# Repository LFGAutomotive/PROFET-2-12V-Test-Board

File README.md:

# Infineon PROFET +2 12V PMIC Test Board
This is a KiCad project for a pcb to test Infineon PROFET +2 12V PMIC packages. This board uses a Raspberry Pi Pico as the main testing MCU.

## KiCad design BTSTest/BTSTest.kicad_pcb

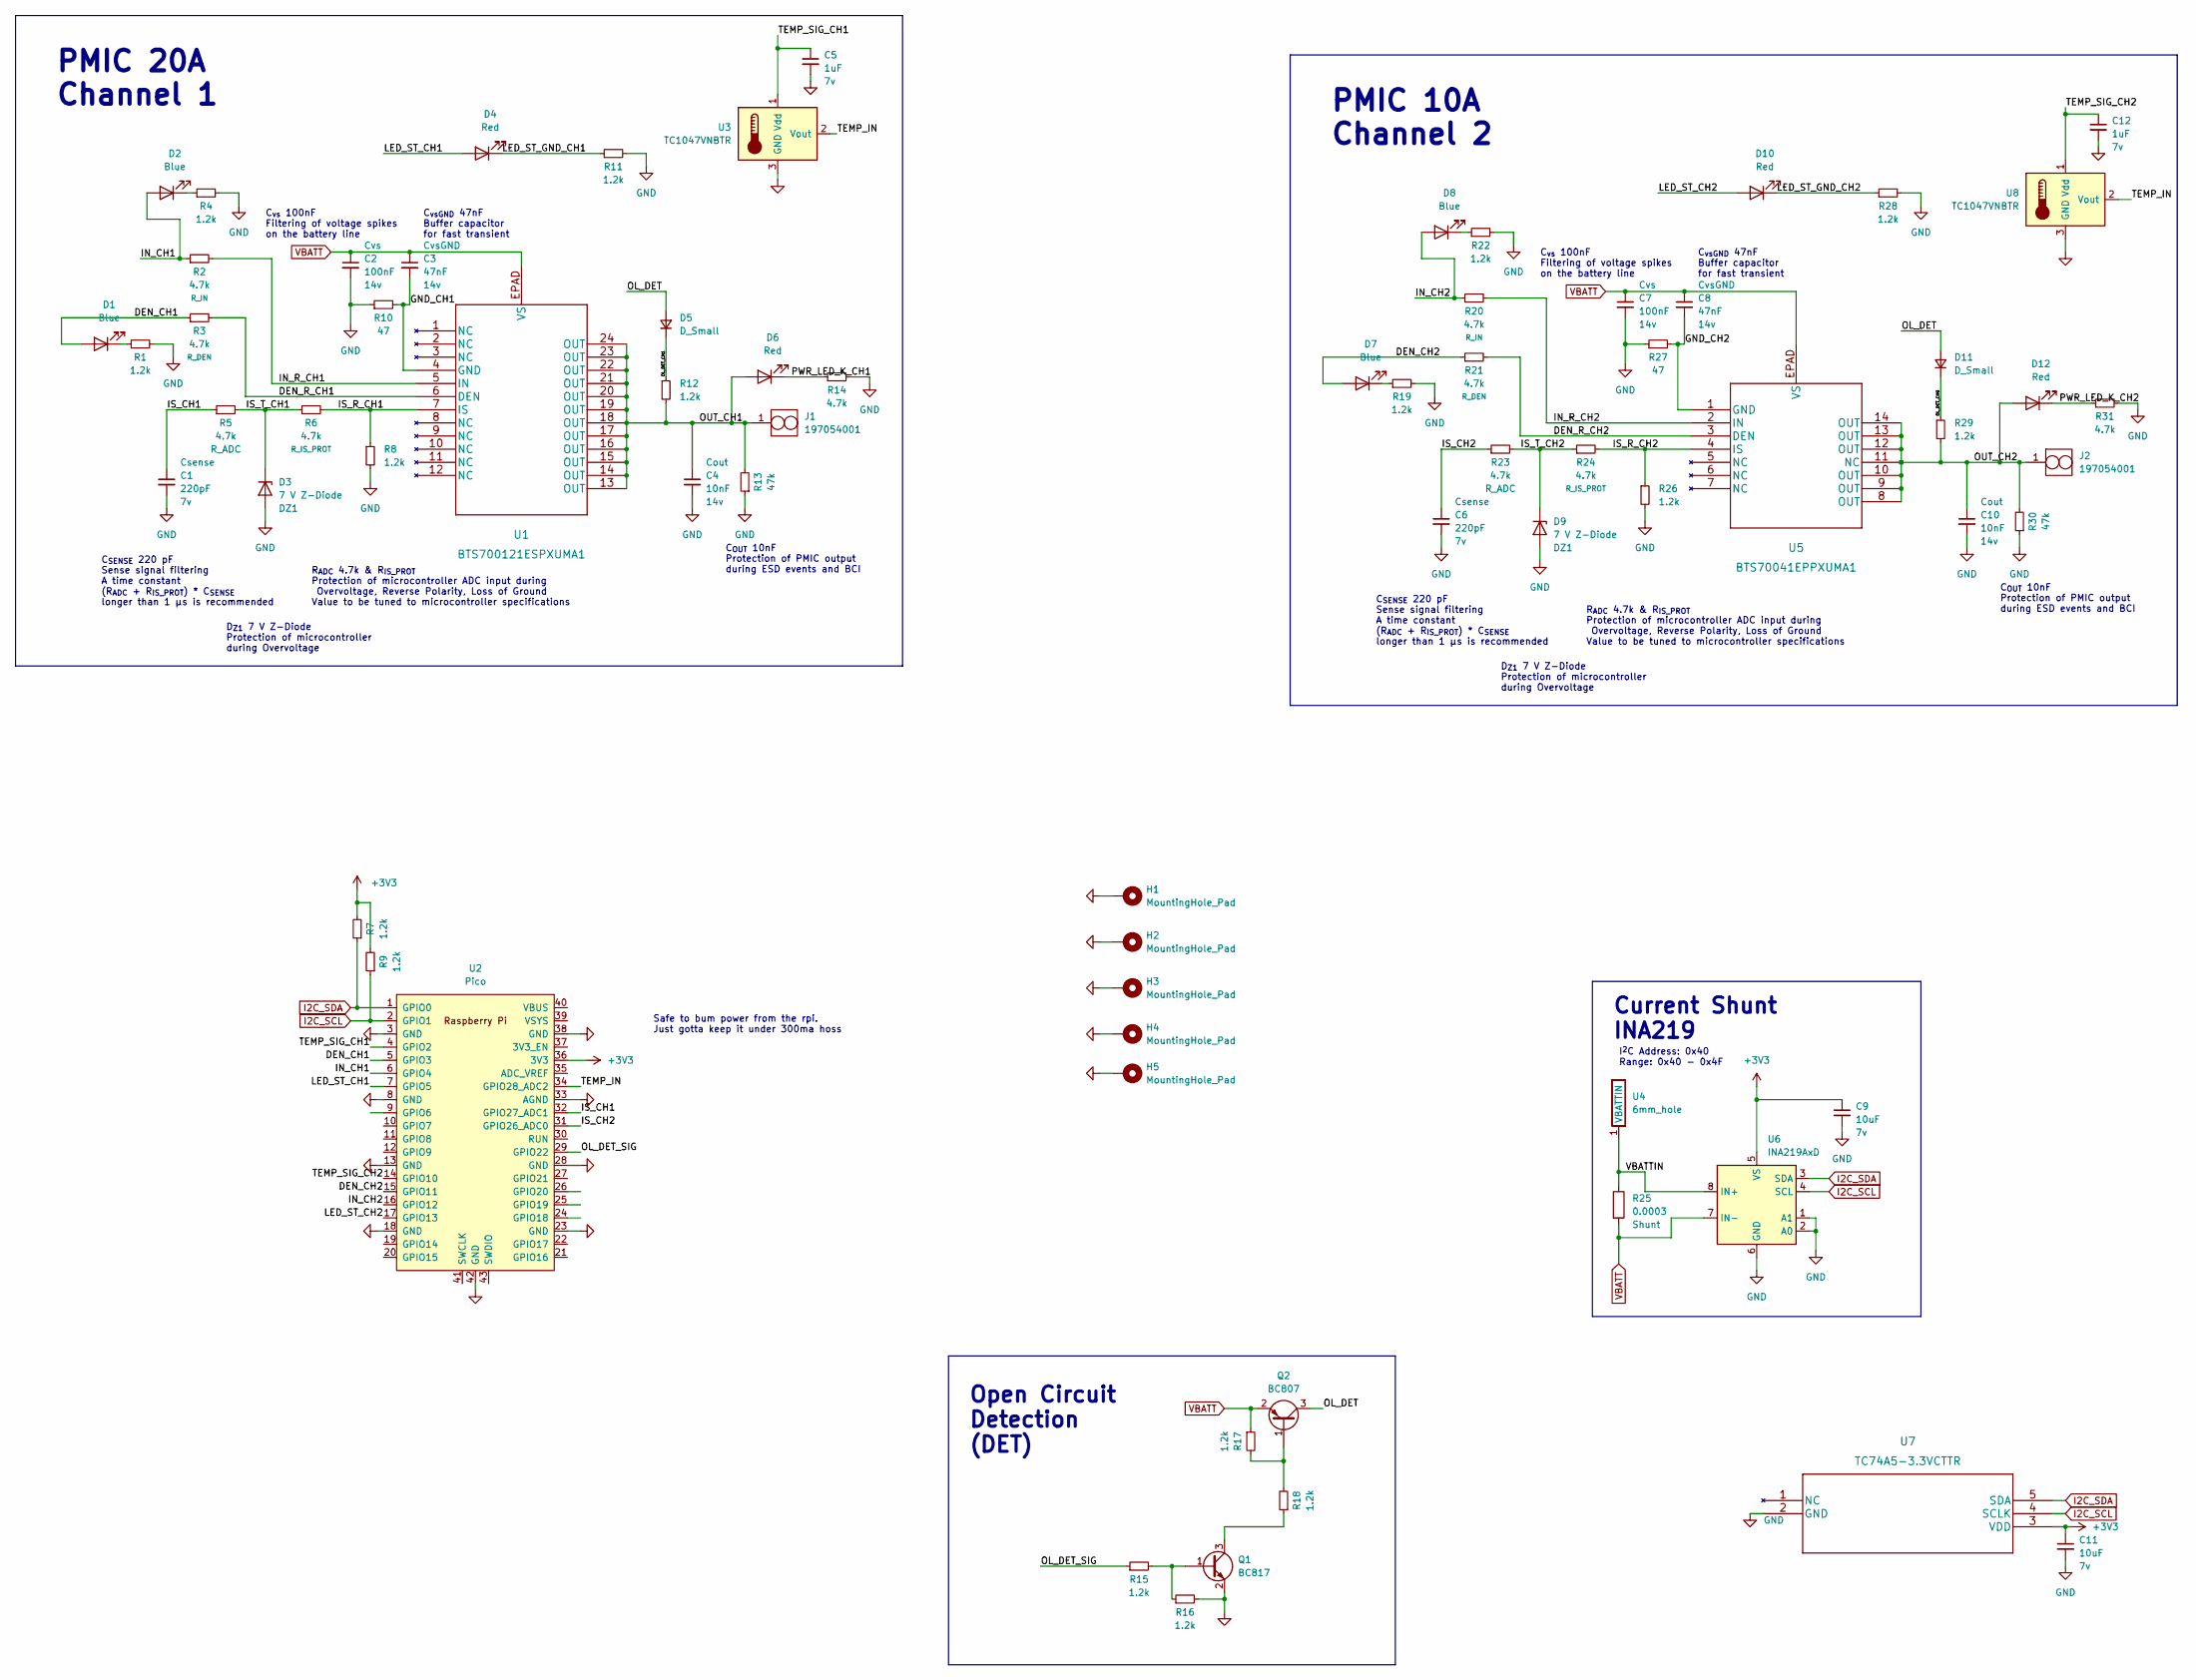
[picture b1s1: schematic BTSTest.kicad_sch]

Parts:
C1, C6: 220pF; C_0603_1608Metric; Voltage 7v
C2, C7: 100nF; C_0603_1608Metric; Voltage 14v
C3, C8: 47nF; C_0603_1608Metric; Voltage 14v
C4, C10: 10nF; C_0603_1608Metric; Voltage 14v
C5, C12: 1uF; C_0603_1608Metric; Voltage 7v
C9, C11: 10uF; C_0603_1608Metric; Voltage 7v
D1, D2, D7, D8: Blue; LED_0603_1608Metric
D3, D9: 7 V Z-Diode; D_SOD-123
D4, D6, D10, D12: Red; LED_0603_1608Metric
D5, D11: D_Small; D_0805_2012Metric
H1, H2, H3, H4: MountingHole_Pad; MountingHole_4.3mm_M4_Pad_TopBottom
H5: MountingHole_Pad; 197054001
J1, J2: 197054001
Q1: BC817; SOT-23
Q2: BC807; SOT-23
R1, R4, R7, R8, R9, R11, R12, R15, R16, R17, R18, R19, R22, R26, R28, R29: 1.2k; R_0603_1608Metric
R2, R3, R5, R6, R14, R20, R21, R23, R24, R31: 4.7k; R_0603_1608Metric
R10, R27: 47; R_0603_1608Metric
R13, R30: 47k; R_0603_1608Metric
R25: 0.0003; 5930
U1: BTS700121ESPXUMA1; PG-TSDSO-24_VIA
U2: Pico; RPi_Pico_SMD_TH
U3, U8: TC1047VNBTR; SOT-23
U4: 6mm_hole; 197054001
U5: BTS70041EPPXUMA1; PG-TSDSO-14-22_VIA
U6: INA219AxD; SOIC-8_3.9x4.9mm_P1.27mm
U7: TC74A5-3.3VCTTR

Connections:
+3V3: C9.1, C11.1, R7.2, R9.2, U2.36 (3V3), U6.5 (VS), U7.3 (VDD)
/DEN_CH1: D1.2 (A), R3.1, U2.5 (GPIO3)
/DEN_CH2: D7.2 (A), R21.1, U2.15 (GPIO11)
/DEN_R_CH1: R3.2, U1.6 (DEN)
/DEN_R_CH2: R21.2, U5.3 (DEN)
/GND_CH1: C3.2, R10.2, U1.4 (GND)
/GND_CH2: C8.2, R27.2, U5.1 (GND)
/IN_CH1: D2.2 (A), R2.1, U2.6 (GPIO4)
/IN_CH2: D8.2 (A), R20.1, U2.16 (GPIO12)
/IN_R_CH1: R2.2, U1.5 (IN)
/IN_R_CH2: R20.2, U5.2 (IN)
/IS_CH1: C1.1, R5.1, U2.32 (GPIO27_ADC1)
/IS_CH2: C6.1, R23.1, U2.31 (GPIO26_ADC0)
/IS_R_CH1: R6.2, R8.1, U1.7 (IS)
/IS_R_CH2: R24.2, R26.1, U5.4 (IS)
/IS_T_CH1: D3.1 (K), R5.2, R6.1
/IS_T_CH2: D9.1 (K), R23.2, R24.1
/LED_ST_CH1: D4.2 (A), U2.7 (GPIO5)
/LED_ST_CH2: D10.2 (A), U2.17 (GPIO13)
/LED_ST_GND_CH1: D4.1 (K), R11.1
/LED_ST_GND_CH2: D10.1 (K), R28.1
/OL_DET: D5.2 (A), D11.2 (A), Q2.3 (C)
/OL_DET_CH1: D5.1 (K), R12.1
/OL_DET_CH9: D11.1 (K), R29.1
/OL_DET_SIG: R15.1, U2.29 (GPIO22)
/OUT_CH1: C4.1, D6.2 (A), J1.1, R12.2, R13.2, U1.13 (OUT), U1.14 (OUT), U1.15 (OUT), U1.16 (OUT), U1.17 (OUT), U1.18 (OUT), U1.19 (OUT), U1.20 (OUT), U1.21 (OUT), U1.22 (OUT), U1.23 (OUT), U1.24 (OUT)
/OUT_CH2: C10.1, D12.2 (A), J2.1, R29.2, R30.2, U5.8 (OUT), U5.9 (OUT), U5.10 (OUT), U5.11 (NC), U5.12 (OUT), U5.13 (OUT), U5.14 (OUT)
/PWR_LED_K_CH1: D6.1 (K), R14.1
/PWR_LED_K_CH2: D12.1 (K), R31.1
/TEMP_IN: U2.34 (GPIO28_ADC2), U3.2 (Vout), U8.2 (Vout)
/TEMP_SIG_CH1: C5.1, U2.4 (GPIO2), U3.1 (Vdd)
/TEMP_SIG_CH2: C12.1, U2.14 (GPIO10), U8.1 (Vdd)
/VBATTIN: R25.1, U4.1 (VBATTIN), U6.8 (IN+)
GND: C1.2, C2.2, C4.2, C5.2, C6.2, C7.2, C9.2, C10.2, C11.2, C12.2, D3.2 (A), D9.2 (A), H1.1, H2.1, H3.1, H4.1, H5.1, Q1.2 (E), R1.2, R4.2, R8.2, R10.1, R11.2, R13.1, R14.2, R16.2, R19.2, R22.2, R26.2, R27.1, R28.2, R30.1, R31.2, U2.3 (GND), U2.8 (GND), U2.13 (GND), U2.18 (GND), U2.23 (GND), U2.28 (GND), U2.33 (AGND), U2.38 (GND), U2.42 (GND), U3.3 (GND), U6.1 (A1), U6.2 (A0), U6.6 (GND), U7.2 (GND), U8.3 (GND)
I2C_SCL: R9.1, U2.2 (GPIO1), U6.4 (SCL), U7.4 (SCLK)
I2C_SDA: R7.1, U2.1 (GPIO0), U6.3 (SDA), U7.5 (SDA)
unnamed: D1.1 (K), R1.1
unnamed: D2.1 (K), R4.1
unnamed: D7.1 (K), R19.1
unnamed: D8.1 (K), R22.1
unnamed: Q1.1 (B), R15.2, R16.1
unnamed: Q1.3 (C), R18.1
unnamed: Q2.1 (B), R17.2, R18.2
VBATT: C2.1, C3.1, C7.1, C8.1, Q2.2 (E), R17.1, R25.2, U1.EPAD (VS), U5.EPAD (VS), U6.7 (IN-)

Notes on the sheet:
R_{ADC} 4.7k & R_{IS_PROT} Protection of microcontroller ADC input during Overvoltage, Reverse Polarity, Loss of Ground Value to be tuned to microcontroller specifications
C_{SENSE} 220 pF Sense signal filtering A time constant (R_{ADC} + R_{IS_PROT}) * C_{SENSE} longer than 1 µs is recommended
PMIC 10A Channel 2
C_{vs} 100nF Filtering of voltage spikes on the battery line
C_{vsGND} 47nF Buffer capacitor for fast transient
I^{2}C Address: 0x40 Range: 0x40 - 0x4F
D_{Z1} 7 V Z-Diode Protection of microcontroller during Overvoltage
Open Circuit Detection (DET)
C_{OUT} 10nF Protection of PMIC output during ESD events and BCI
Current Shunt INA219
Safe to bum power from the rpi. Just gotta keep it under 300ma hoss
PMIC 20A Channel 1

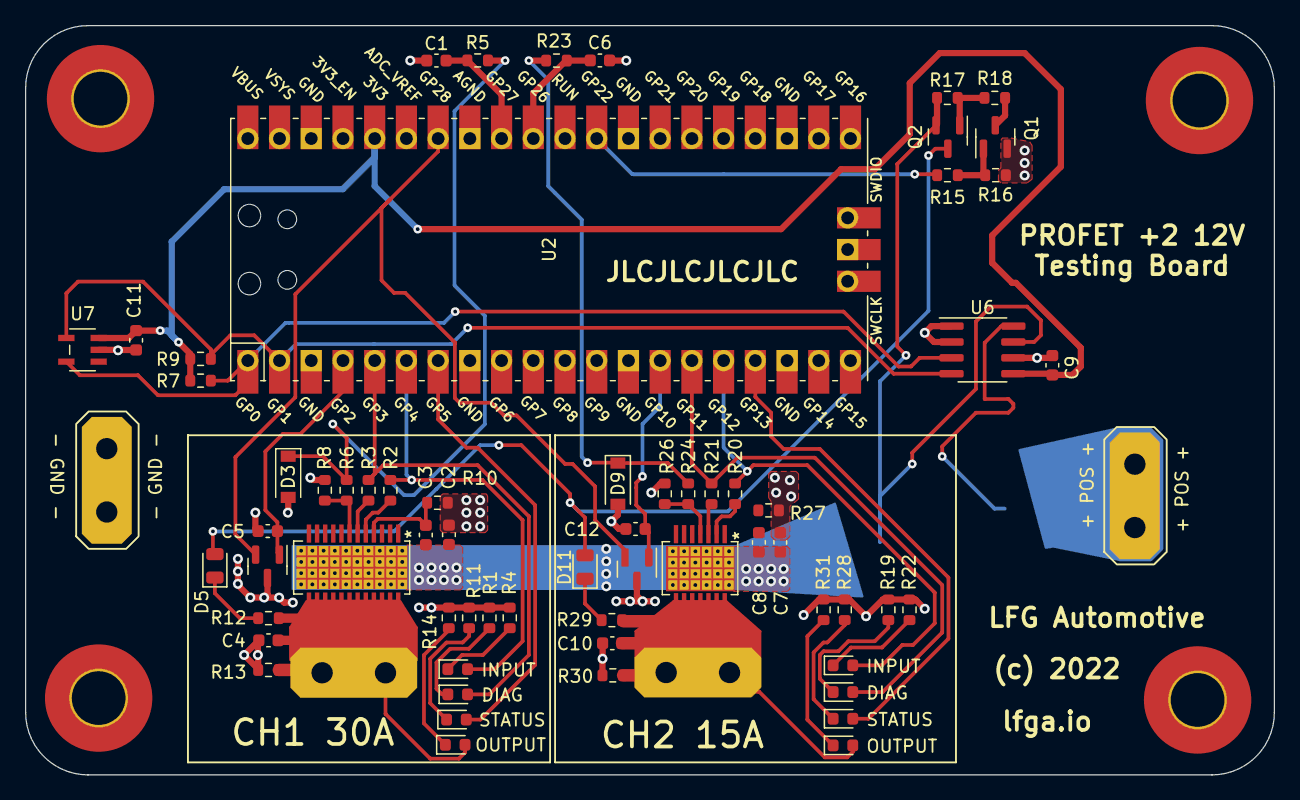
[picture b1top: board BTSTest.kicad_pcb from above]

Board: 2 copper layers, 100.0 x 60.0 mm, 72 parts (1 on the bottom side), 44 nets.

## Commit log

2022-09-20 Add readme

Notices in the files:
BTSTest/BTSTest.kicad_pcb:
(c) 2022
parts and their libraries:
Copyright 2021 Accelerated Designs. All rights reserved.
